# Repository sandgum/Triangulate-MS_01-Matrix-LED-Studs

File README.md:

# MatrixStuds

## Description
Tiny 10x10mm ear studs (inspired by Mitxela) with 16 LEDs on each, arranged in a 4x4 matrix. Each matrix is controlled by an Analog Devices MAX32660 microcontroller paired with a Bosch BMA530 accelerometer to react to orientation changes. Each stud features a tiny 3.7v-3.3v step-down converter to accept rechargeable Li-ion cells. All tied up together in a CNC'd steel enclosure.

## PCB (Studs)
### Overview
* 4-layer double-stacked rigid PCB (8 layers when assembled)
* Matrix on one "part" of PCB, other electronics on other "part"
* Features interconnect pads on back of each PCB to interface between the two "parts"
* 0.4mm thickness, 0.8mm total stacked thickness
* Features 1mm pads for programming, power pins

### Schematic

### PCB Layout

*Top Layer*

*Bottom Layer*

*3D Model (Bottom Side)*

*3D Model (Top Side)*

## PCB (Charging Board)
## Overview
* 4-layer double-stacked rigid PCB (8 layers when assembled)
* Side 1:
*   Battery charging circuitry for two batteries (fuel gauge and charger)
*   USB-C Port
*   ATMega328P microcontroller for controlling lights
* Side 2:
*   9x WS2812B 2mm NeoPixel Lights
*   Reset SPDT switch for MCU

### Schematic

### PCB Layout

*Top Layer*

*Bottom Layer*

*3D Model (Top Side)*

*3D Model (Bottom Side)*

## Enclosure
### Overview (Studs)
* CNC stainless steel construction
* Two-part design, one for battery side, one for top side
* Translucent PP diffuser over LED matrix
* Push-lock mechanism two secure both sides
* Permanent power wire going from battery side to top side in accent colour
* Points on back of top side for rotational stability while on ear

### Overview (Charging Dock)
* CNC steel upper construction, 3D-printed plastic lower construction
* Battery charging GND connection made through upper case, positive connection made through insulated copper springs
* Magnets to secure studs
* USB-C charging, SoC indication through adressable RGB strip

### Images (Studs)

### Images (Charging Dock)

## Bill of Materials (Coming soon)

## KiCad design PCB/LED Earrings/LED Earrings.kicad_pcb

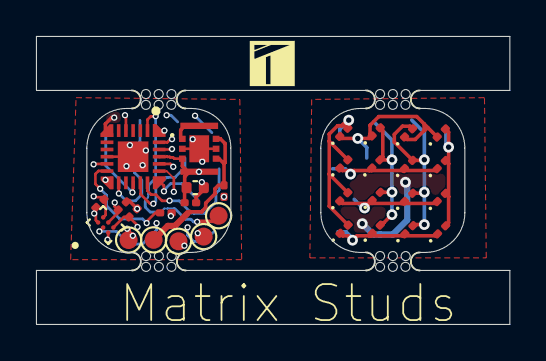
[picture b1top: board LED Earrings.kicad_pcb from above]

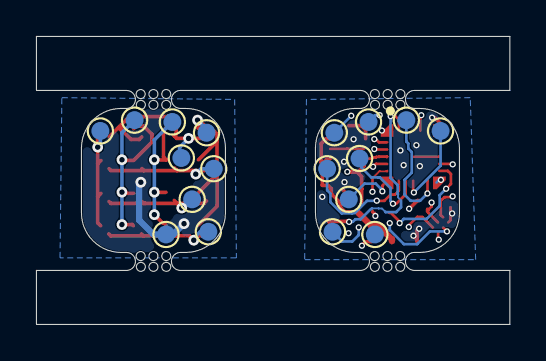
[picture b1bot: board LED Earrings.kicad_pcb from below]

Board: 4 copper layers, 26.3 x 16.0 mm, 53 parts (18 on the bottom side), 26 nets.

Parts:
A1: BMA530; BGA6N40P3X2_120X80X59
C1, C5: 1uF; C_0201_0603Metric
C2: 10uF; C_0402_1005Metric
C3: 4.7uF; C_0201_0603Metric
C4: 100nF; C_0201_0603Metric
D1, D2, D3, D4, D5, D6, D7, D8, D9, D10, D11, D12, D13, D14, D15, D16: LED; LED_0201_0603Metric
R1, R2: 4.7k; R_0201_0603Metric
TP1: SWDIO; TestPoint_Pad_D1.0mm
TP2: SWDCLK; TestPoint_Pad_D1.0mm
TP3: BAT+; TestPoint_Pad_D1.0mm
TP4: BAT-; TestPoint_Pad_D1.0mm
TP5: VIO; TestPoint_Pad_D1.0mm
TP6, TP13: P0.8; TestPoint_Pad_D1.0mm
TP7, TP15: P0.10; TestPoint_Pad_D1.0mm
TP8, TP16: P0.7; TestPoint_Pad_D1.0mm
TP9, TP17: P0.6; TestPoint_Pad_D1.0mm
TP10, TP18: P0.5; TestPoint_Pad_D1.0mm
TP11: GND; TestPoint_Pad_D1.0mm
TP12, TP23: P0.9; TestPoint_Pad_D1.0mm
TP14, TP21: P0.11; TestPoint_Pad_D1.0mm
TP19, TP20: P0.12; TestPoint_Pad_D1.0mm
TP22: GND1; TestPoint_Pad_D1.0mm
U1: MAX32660GTG+T; 21-100264_90-100089_MXM
U2: XCL202B331ER-G; CONV_XCL206B333CR-G
mouse-bite-1mm-3mm, mouse-bite-1mm-3mm#2, mouse-bite-1mm-3mm#3, mouse-bite-1mm-3mm#4: VAL**; mouse-bite-1mm-3mm

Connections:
+3V3: A1.3 (INT2), A1.6 (VDD), C1.1, C2.1, C4.1, R1.2, R2.2, TP5.1, U1.11 (VDD), U1.22 (VDD), U2.3 (Vout), U2.8 (L2)
GND: A1.1 (VSS), C1.2, C2.2, C3.2, C4.2, C5.2, TP4.1, TP11.1, U1.7 (VSS), U1.10 (VSS), U1.25 (EPAD), U2.2 (Vss), U2.5 (Vss)
unnamed: A1.2 (INT1), U1.21 (P0.4)
unnamed: A1.5 (SCL), R1.1, U1.24 (P0.2)
unnamed: A1.4 (SDA), R2.1, U1.23 (P0.3)
unnamed: D1.2 (A), D2.2 (A), D3.2 (A), D4.2 (A), TP19.1
unnamed: D1.1 (K), D5.1 (K), D9.1 (K), D13.1 (K), TP7.1
unnamed: D5.2 (A), D6.2 (A), D7.2 (A), D8.2 (A), TP23.1
unnamed: D9.2 (A), D10.2 (A), D11.2 (A), D12.2 (A), TP6.1
unnamed: D2.1 (K), D6.1 (K), D10.1 (K), D14.1 (K), TP8.1
unnamed: D3.1 (K), D7.1 (K), D11.1 (K), D15.1 (K), TP9.1
unnamed: D4.1 (K), D8.1 (K), D12.1 (K), D16.1 (K), TP10.1
unnamed: D13.2 (A), D14.2 (A), D15.2 (A), D16.2 (A), TP21.1
unnamed: TP2.1, U1.2 (P0.0)
unnamed: TP1.1, U1.1 (P0.1)
unnamed: TP18.1, U1.20 (P0.5)
unnamed: TP17.1, U1.19 (P0.6)
unnamed: TP16.1, U1.18 (P0.7)
unnamed: TP13.1, U1.14 (P0.8)
unnamed: TP12.1, U1.13 (P0.9)
unnamed: TP15.1, U1.17 (P0.10)
unnamed: TP14.1, U1.16 (P0.11)
unnamed: TP20.1, U1.5 (P0.12)
unnamed: C5.1, U1.12 (VCORE)
unnamed: U2.1 (Lx), U2.7 (L1)
VCC: C3.1, TP3.1, U2.4 (CE), U2.6 (Vin)

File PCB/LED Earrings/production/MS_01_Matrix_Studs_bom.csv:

Designator,Footprint,Quantity,Value,LCSC Part #
A1,BGA6N40P3X2_120X80X59,1,BMA530,
"C1, C5",0201,2,1uF,
C2,0402,1,10uF,
C3,0201,1,4.7uF,
C4,0201,1,100nF,
"D1, D10, D11, D12, D13, D14, D15, D16, D2, D3, D4, D5, D6, D7, D8, D9",0201,16,LED,
"MOUSE-BITE-1MM-3MM_4, MOUSE-BITE-1MM-3MM_3, MOUSE-BITE-1MM-3MM_2, MOUSE-BITE-1MM-3MM",mouse-bite-1mm-3mm,4,VAL**,
"R1, R2",0201,2,4.7k,
TP1,TestPoint_Pad_D1.0mm,1,SWDIO,
"TP10, TP18",TestPoint_Pad_D1.0mm,2,P0.5,
TP11,TestPoint_Pad_D1.0mm,1,GND,
"TP12, TP23",TestPoint_Pad_D1.0mm,2,P0.9,
"TP13, TP6",TestPoint_Pad_D1.0mm,2,P0.8,
"TP14, TP21",TestPoint_Pad_D1.0mm,2,P0.11,
"TP15, TP7",TestPoint_Pad_D1.0mm,2,P0.10,
"TP16, TP8",TestPoint_Pad_D1.0mm,2,P0.7,
"TP17, TP9",TestPoint_Pad_D1.0mm,2,P0.6,
"TP19, TP20",TestPoint_Pad_D1.0mm,2,P0.12,
TP2,TestPoint_Pad_D1.0mm,1,SWDCLK,
TP22,TestPoint_Pad_D1.0mm,1,GND1,
TP3,TestPoint_Pad_D1.0mm,1,BAT+,
TP4,TestPoint_Pad_D1.0mm,1,BAT-,
TP5,TestPoint_Pad_D1.0mm,1,VIO,
U1,21-100264_90-100089_MXM,1,MAX32660GTG+T,
U2,CONV_XCL206B333CR-G,1,XCL202B331ER-G,

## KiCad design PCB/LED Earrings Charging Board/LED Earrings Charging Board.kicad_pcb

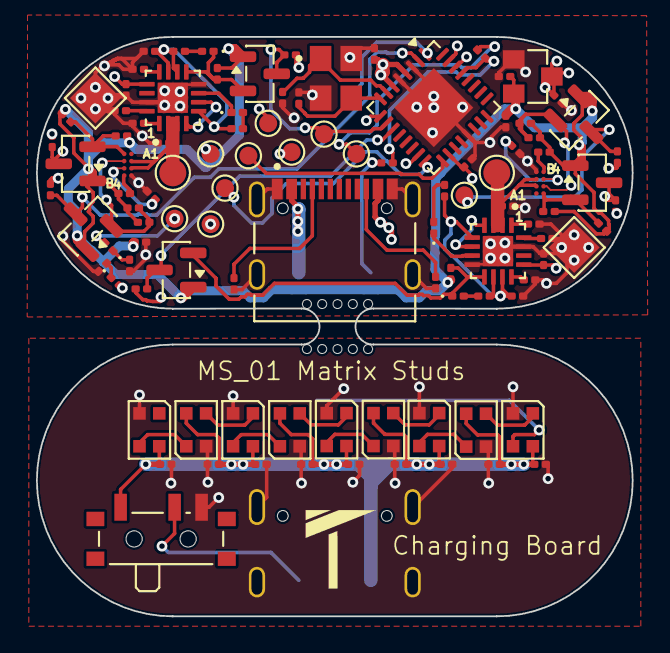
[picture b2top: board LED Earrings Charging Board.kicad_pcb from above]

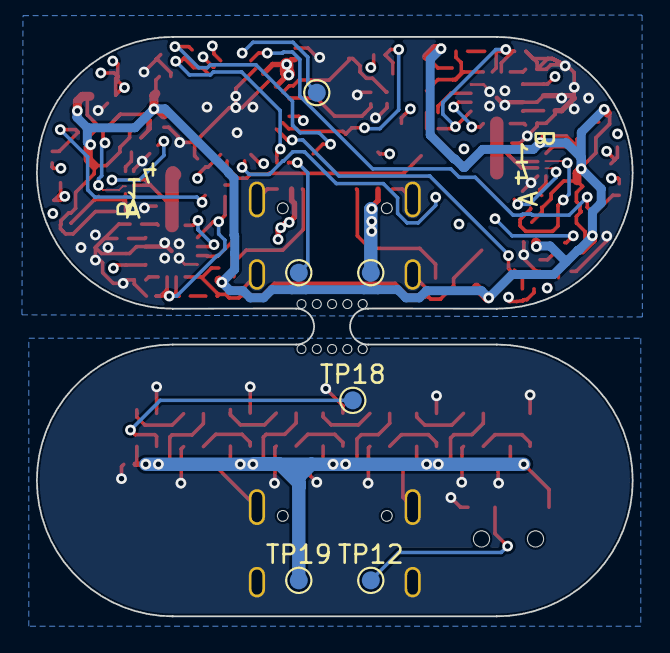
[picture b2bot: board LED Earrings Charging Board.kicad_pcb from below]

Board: 4 copper layers, 33.1 x 32.2 mm, 110 parts (6 on the bottom side), 62 nets.

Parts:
C1, C3, C5, C6, C57, C58, C59, C60: 1uF; C_0201_0603Metric
C2, C4: 4.7uF; C_0201_0603Metric
C7, C8: 22pF; C_0201_0603Metric
C9, C10: 10pF; C_0201_0603Metric
C11, C12, C13, C14, C15, C16, C17, C18, C19, C20: 100nF; C_0201_0603Metric
D1, D2, D3, D4, D5, D6: LED; LED_0201_0603Metric
D9, D10, D11, D12, D13, D14, D16, D17, D18: WS2812B-2020; LED_WS2812B-2020_PLCC4_2.0x2.0mm
J1, J1#2: TYPE-C-31-M-12; HRO_TYPE-C-31-M-12
Q3, Q4, Q5, Q6, Q7, Q8: BSS138; SOT-23
R1, R2, R11, R12: 1.5k; R_0201_0603Metric
R3, R9: 10k; R_0201_0603Metric
R4, R5, R8, R10: 1.18k; R_0201_0603Metric
R6, R7: 5.1k; R_0201_0603Metric
R22, R23, R24, R25, R26, R27, R28, R29, R30, R31, R32, R33, R34, R35, R36, R37, R38, R39, R40, R41, R42, R43, R44: 10K; R_0201_0603Metric
SW1: SW_SPDT; SW_SPDT_PCM12
TP1, TP3: Battery+; TestPoint_Pad_D1.5mm
TP2, TP4: GND; TestPoint_Pad_2.0x2.0mm
TP5: MOSI; TestPoint_Pad_D1.0mm
TP6: MISO; TestPoint_Pad_D1.0mm
TP7: SCK; TestPoint_Pad_D1.0mm
TP8: TX; TestPoint_Pad_D1.0mm
TP9: RX; TestPoint_Pad_D1.0mm
TP10: DTR; TestPoint_Pad_D1.0mm
TP11: 5V; TestPoint_Pad_D1.0mm
TP12: RESET_2; TestPoint_Pad_D1.0mm
TP13: DOUT_MCU; TestPoint_Pad_D1.0mm
TP14, TP16, TP17: TestPoint; TestPoint_Pad_D1.0mm
TP18: DIN_LED; TestPoint_Pad_D1.0mm
TP19: VCC_LED; TestPoint_Pad_D1.0mm
TP20: VCC_O_LED; TestPoint_Pad_D1.0mm
TP23: RESET_1; TestPoint_Pad_D1.0mm
U1, U2: BQ24075RGTR; QFN50P300X300X100-17N
U3: ATmega328P-M; QFN-32-1EP_5x5mm_P0.5mm_EP3.1x3.1mm
U4: XC6206P332MR-G-SOT23; SOT-23
U12, U13: MAX17048X+T10; 21-0555B_W80B1-1_MXM
Y1: X322516MLB4SI; OSC_X322516MLB4SI

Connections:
3V3: C5.1, C58.1, C59.1, Q3.1 (G), Q4.1 (G), Q5.1 (G), Q6.1 (G), Q7.1 (G), Q8.1 (G), R22.1, R24.1, R26.1, R28.1, R30.2, R31.2, R34.2, R35.2, R36.2, R37.2, R41.1, R43.1, U4.2 (VOUT)
BATCHG1: Q7.3 (D), R42.1, TP14.1 (1_1), U3.10 (PD6)
BATCHG2: Q8.3 (D), R44.1, U3.11 (PD7)
GND: C1.2, C2.2, C3.2, C4.2, C5.2, C6.2, C7.2, C8.2, C9.2, C10.2, C57.2, C58.2, C59.2, C60.2, J1.A1_B12 (GND), J1.B1_A12 (GND), J1.S1 (SHIELD), J1.S2 (SHIELD), J1.S3 (SHIELD), J1.S4 (SHIELD), R3.2, R4.2, R5.2, R6.2, R7.2, R8.2, R9.2, R10.2, R33.1, R38.1, R39.1, R40.1, TP2.1 (1_1), TP4.1 (1_1), U1.8 (VSS), U1.15 (SYSOFF), U1.17 (EXP), U2.8 (VSS), U2.15 (SYSOFF), U2.17 (EXP), U3.3 (GND), U3.5 (GND), U3.21 (GND), U3.33 (GND), U4.1 (VSS), U12.A4 (GND), U13.A4 (GND), Y1.2, Y1.4
unnamed: C11.1, TP10.1 (1_1)
unnamed: D1.2 (A), R1.1
unnamed: D1.1 (K), U1.7 (~PGOOD)
unnamed: D2.2 (A), R2.1
unnamed: D2.1 (K), Q7.2 (S), R41.2, U1.9 (~CHG)
unnamed: D3.2 (A), R11.1
unnamed: D3.1 (K), U2.7 (~PGOOD)
unnamed: D4.2 (A), R12.1
unnamed: D4.1 (K), Q8.2 (S), R43.2, U2.9 (~CHG)
unnamed: D5.2 (A), TP8.1 (1_1), U3.30 (PD0)
unnamed: D5.1 (K), R39.2
unnamed: D6.2 (A), TP9.1 (1_1), U3.31 (PD1)
unnamed: D6.1 (K), R40.2
unnamed: D10.3 (DIN), D14.1 (DOUT)
unnamed: D9.3 (DIN), D10.1 (DOUT)
unnamed: C12.1, C13.1, C14.1, C15.1, C16.1, C17.1, C18.1, C19.1, C20.1, D9.4 (VDD), D10.4 (VDD), D11.4 (VDD), D12.4 (VDD), D13.4 (VDD), D14.4 (VDD), D16.4 (VDD), D17.4 (VDD), D18.4 (VDD), SW1.1 (A), TP19.1 (1_1)
unnamed: C12.2, C13.2, C14.2, C15.2, C16.2, C17.2, C18.2, C19.2, C20.2, D9.2 (VSS), D10.2 (VSS), D11.2 (VSS), D12.2 (VSS), D13.2 (VSS), D14.2 (VSS), D16.2 (VSS), D17.2 (VSS), D18.2 (VSS), J1#2.S1 (SHIELD), J1#2.S2 (SHIELD), J1#2.S3 (SHIELD), J1#2.S4 (SHIELD), SW1.3 (C)
unnamed: D11.3 (DIN), D12.1 (DOUT)
unnamed: D11.1 (DOUT), D18.3 (DIN)
unnamed: D12.3 (DIN), TP18.1 (1_1)
unnamed: D13.3 (DIN), D17.1 (DOUT)
unnamed: D13.1 (DOUT), D14.3 (DIN)
unnamed: D9.1 (DOUT), D16.3 (DIN)
unnamed: D17.3 (DIN), D18.1 (DOUT)
unnamed: J1.A5 (CC1), R7.1
unnamed: J1.B5 (CC2), R6.1
unnamed: Q3.2 (S), R22.2, R37.1, U13.B2 (SCL)
unnamed: Q4.2 (S), R24.2, R36.1, U13.B1 (SDA)
unnamed: Q5.2 (S), R26.2, R34.1, U12.B1 (SDA)
unnamed: Q6.2 (S), R28.2, R35.1, U12.B2 (SCL)
unnamed: R32.1, TP23.1 (1_1)
unnamed: SW1.2 (B), TP12.1 (1_1)
unnamed: C57.1, TP1.1 (1_1), U1.2 (BAT_2), U1.3 (BAT_3), U12.A2 (CELL), U12.A3 (VDD)
unnamed: U1.4 (~CE), U1.6 (EN1)
unnamed: C2.1, R1.2, R2.2, U1.5 (EN2), U1.10 (OUT_10), U1.11 (OUT_11)
unnamed: R4.1, U1.12 (ILIM)
unnamed: R5.1, U1.16 (ISET)
unnamed: R3.1, U1.1 (TS)
unnamed: U2.4 (~CE), U2.6 (EN1)
unnamed: C4.1, R11.2, R12.2, U2.5 (EN2), U2.10 (OUT_10), U2.11 (OUT_11)
unnamed: R8.1, U2.12 (ILIM)
unnamed: R10.1, U2.16 (ISET)
unnamed: R9.1, U2.1 (TS)
unnamed: TP5.1 (1_1), U3.15 (PB3)
unnamed: TP6.1 (1_1), U3.16 (PB4)
unnamed: TP7.1 (1_1), U3.17 (PB5)
unnamed: TP13.1 (1_1), U3.1 (PD3)
unnamed: C7.1, U3.7 (XTAL1/PB6), Y1.1
unnamed: C8.1, U3.8 (XTAL2/PB7), Y1.3
unnamed: C11.2, R32.2, U3.29 (~RESET/PC6)
unnamed: R30.1, U12.B4 (*ALRT)
unnamed: R33.2, U12.B3 (QSTRT)
unnamed: R31.1, U13.B4 (*ALRT)
unnamed: C60.1, TP3.1 (1_1), U2.2 (BAT_2), U2.3 (BAT_3), U13.A2 (CELL), U13.A3 (VDD)
unnamed: R38.2, U13.B3 (QSTRT)
SCL: Q3.3 (D), Q6.3 (D), R23.1, R29.1, TP16.1 (1_1), U3.2 (PD4)
SDA: Q4.3 (D), Q5.3 (D), R25.1, R27.1, TP17.1 (1_1), U3.9 (PD5)
VCC: C1.1, C3.1, C6.1, C9.1, C10.1, J1.A4_B9 (VBUS), J1.B4_A9 (VBUS), R23.2, R25.2, R27.2, R29.2, R42.2, R44.2, TP11.1 (1_1), TP20.1 (1_1), U1.13 (IN), U2.13 (IN), U3.4 (VCC), U3.6 (VCC), U3.18 (AVCC), U4.3 (VIN)

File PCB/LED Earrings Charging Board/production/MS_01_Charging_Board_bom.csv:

Designator,Footprint,Quantity,Value,LCSC Part #
"C1, C3, C5, C57, C58, C59, C6, C60",0201,8,1uF,
"C10, C9",0201,2,10pF,
"C11, C12, C13, C14, C15, C16, C17, C18, C19, C20",0201,10,100nF,
"C2, C4",0201,2,4.7uF,
"C7, C8",0201,2,22pF,
"D1, D2, D3, D4, D5, D6",0201,6,LED,
"D10, D11, D12, D13, D14, D16, D17, D18, D9",LED_WS2812B-2020_PLCC4_2.0x2.0mm,9,WS2812B-2020,
"J1_2, J1",HRO_TYPE-C-31-M-12,2,TYPE-C-31-M-12,
"Q3, Q4, Q5, Q6, Q7, Q8",SOT-23,6,BSS138,
"R1, R11, R12, R2",0201,4,1.5k,
"R10, R4, R5, R8",0201,4,1.18k,
"R22, R23, R24, R25, R26, R27, R28, R29, R3, R30, R31, R32, R33, R34, R35, R36, R37, R38, R39, R40, R41, R42, R43, R44, R9",0201,25,10K,
"R6, R7",0201,2,5.1k,
SW1,SW_SPDT_PCM12,1,SW_SPDT,
"TP1, TP3",TestPoint_Pad_D1.5mm,2,Battery+,
TP10,TestPoint_Pad_D1.0mm,1,DTR,
TP11,TestPoint_Pad_D1.0mm,1,5V,
TP12,TestPoint_Pad_D1.0mm,1,RESET_2,
TP13,TestPoint_Pad_D1.0mm,1,DOUT_MCU,
"TP14, TP16, TP17",TestPoint_Pad_D1.0mm,3,TestPoint,
TP18,TestPoint_Pad_D1.0mm,1,DIN_LED,
TP19,TestPoint_Pad_D1.0mm,1,VCC_LED,
"TP2, TP4",TestPoint_Pad_2.0x2.0mm,2,GND,
TP20,TestPoint_Pad_D1.0mm,1,VCC_O_LED,
TP23,TestPoint_Pad_D1.0mm,1,RESET_1,
TP5,TestPoint_Pad_D1.0mm,1,MOSI,
TP6,TestPoint_Pad_D1.0mm,1,MISO,
TP7,TestPoint_Pad_D1.0mm,1,SCK,
TP8,TestPoint_Pad_D1.0mm,1,TX,
TP9,TestPoint_Pad_D1.0mm,1,RX,
"U1, U2",QFN50P300X300X100-17N,2,BQ24075RGTR,
"U12, U13",21-0555B_W80B1-1_MXM,2,MAX17048X+T10,
U3,QFN-32-1EP_5x5mm_P0.5mm_EP3.1x3.1mm,1,ATmega328P-M,
U4,SOT-23,1,XC6206P332MR-G-SOT23,XC6206P332MR-G
Y1,OSC_X322516MLB4SI,1,X322516MLB4SI,

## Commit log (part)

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2026-03-22 Add Project Journal
2026-04-04 Revise README with detailed PCB and enclosure info
    Updated the description and added sections for PCB and Enclosure details, including images.
2026-04-20 Charging Board PCB, CAD Models
2026-04-20 Add schematic and PCB layout sections to README
    Added schematic and PCB layout sections for the charging board.
2026-05-03 Update PCB and enclosure sections in README
2026-05-03 Update README with new images of charging dock
2026-05-03 Updated CAD files with finished charging dock
2026-06-27 Imported Journal from Stasis
